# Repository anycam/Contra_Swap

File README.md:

# Contra_Swap
Contra Mechanical Keyboard Mod

Adding hotswap sockets pads, optional rotary encoder, oled screen and expansion points for uC's like nRFMicro.
Layout change made for 2x2u split space bars.
Still ProMicro compatibile, orientation changed, DAUGHTERBOARD REQUIRED !
Easy type C convertion.

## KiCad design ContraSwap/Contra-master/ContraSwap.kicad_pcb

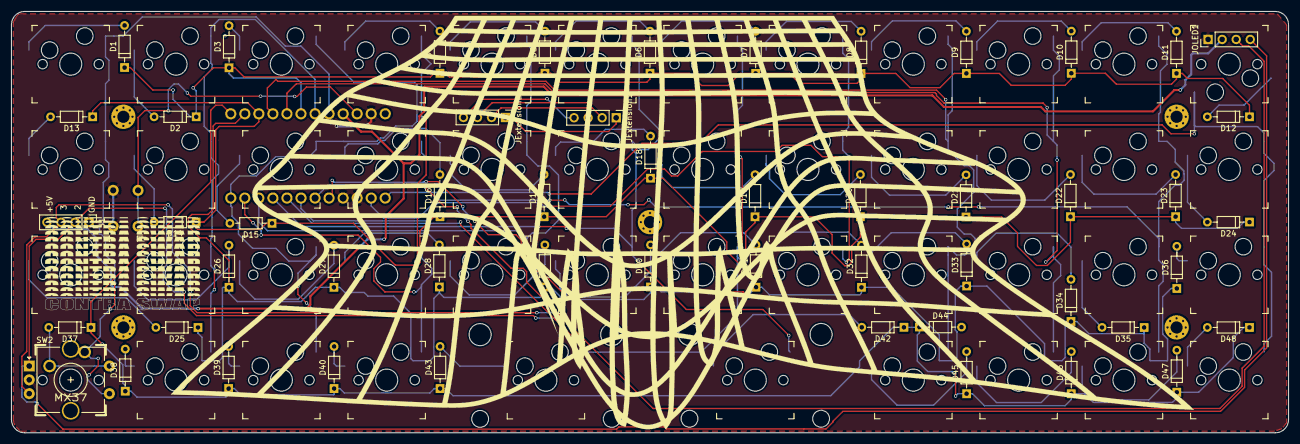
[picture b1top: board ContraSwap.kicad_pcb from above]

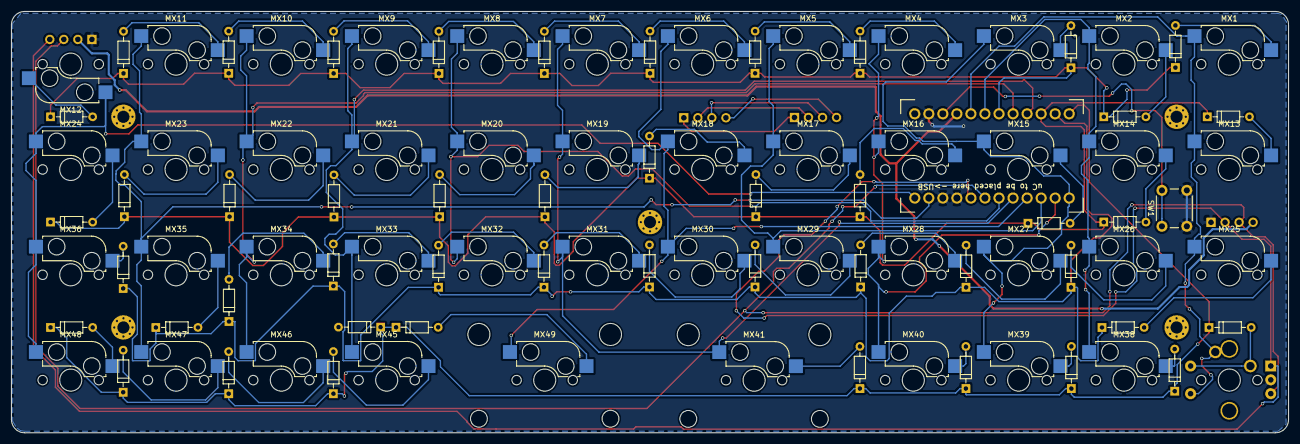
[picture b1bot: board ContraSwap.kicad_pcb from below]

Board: 2 copper layers, 231.0 x 76.2 mm, 102 parts (2 on the bottom side), 71 nets.

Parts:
D1, D2, D3, D4, D5, D6, D7, D8, D9, D10, D11, D12, D13, D14, D15, D16, D17, D18, D19, D20, D21, D22, D23, D24, D25, D26, D27, D28, D29, D30, D31, D32, D33, D34, D35, D36, D37, D38, D39, D40, D42, D43, D44, D45, D46, D47, D48: 1N4148; D_DO-35_SOD27_P7.62mm_Horizontal-DoubleSided
H1, H2: MountingHole; Stabilizer_MX_2u
J1: Conn_01x04; PinHeader_1x04_P2.54mm_Vertical
JExtension1: Conn_01x04; PinHeader_1x04_P2.54mm_Vertical
JExtensionL1: Conn_01x04; PinHeader_1x04_P2.54mm_Vertical
JOLED1: Conn_01x04; PinHeader_1x04_P2.54mm_Vertical
MX1, MX2, MX3, MX4, MX5, MX6, MX7, MX8, MX9, MX10, MX11, MX12, MX13, MX14, MX15, MX16, MX17, MX18, MX19, MX20, MX21, MX22, MX23, MX24, MX25, MX26, MX27, MX28, MX29, MX30, MX31, MX32, MX33, MX34, MX35, MX36, MX38, MX39, MX40, MX45, MX46, MX47, MX48: MX-1U; Kailh_socket_MX
MX37: MX-1U; MX_PCB_100H
MX41, MX49: MX-2U; Kailh_socket_MX
SW1: SW_PUSH; SW_PUSH_6mm
SW2: Rotary_Encoder_Switch; RotaryEncoder_Alps_EC11E-Switch_Vertical_H20mm_CircularMoun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
U1: ProMicro; pro_micro

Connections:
+5V: J1.4, JOLED1.2, U1.21
COL0: MX1.1, MX13.1, MX25.1, MX37.1, SW2.S1, U1.20
COL1: MX2.1, MX14.1, MX26.1, MX38.1, U1.19
COL2: MX3.1, MX15.1, MX27.1, MX39.1, U1.12
COL3: MX4.1, MX16.1, MX28.1, MX40.1, U1.11
COL4: MX5.1, MX17.1, MX29.1, U1.10
COL5: MX6.1, MX18.1, MX30.1, MX49.1, U1.9
COL6: MX7.1, MX19.1, MX31.1, MX41.1, U1.8
COL7: MX8.1, MX20.1, MX32.1, U1.7
COL8: MX9.1, MX21.1, MX33.1, MX45.1, U1.16
COL9: MX10.1, MX22.1, MX34.1, MX46.1, U1.17
COL10: MX11.1, MX23.1, MX35.1, MX47.1, U1.2
COL11: MX12.1, MX24.1, MX36.1, MX48.1, U1.1
GND: J1.1, JOLED1.1, SW1.2, SW2.C, U1.3, U1.4, U1.23
unnamed: D1.2, MX1.2
unnamed: D2.2, MX2.2
unnamed: D3.2, MX3.2
unnamed: D4.2, MX4.2
unnamed: D5.2, MX5.2
unnamed: D6.2, MX6.2
unnamed: D7.2, MX7.2
unnamed: D8.2, MX8.2
unnamed: D9.2, MX9.2
unnamed: D10.2, MX10.2
unnamed: D11.2, MX11.2
unnamed: D12.2, MX12.2
unnamed: D13.2, MX13.2
unnamed: D14.2, MX14.2
unnamed: D15.2, MX15.2
unnamed: D16.2, MX16.2
unnamed: D17.2, MX17.2
unnamed: D18.2, MX18.2
unnamed: D19.2, MX19.2
unnamed: D20.2, MX20.2
unnamed: D21.2, MX21.2
unnamed: D22.2, MX22.2
unnamed: D23.2, MX23.2
unnamed: D24.2, MX24.2
unnamed: D25.2, MX25.2
unnamed: D26.2, MX26.2
unnamed: D27.2, MX27.2
unnamed: D28.2, MX28.2
unnamed: D29.2, MX29.2
unnamed: D30.2, MX30.2
unnamed: D31.2, MX31.2
unnamed: D32.2, MX32.2
unnamed: D33.2, MX33.2
unnamed: D34.2, MX34.2
unnamed: D35.2, MX35.2
unnamed: D36.2, MX36.2
unnamed: D37.2, MX37.2, SW2.S2
unnamed: D38.2, MX38.2
unnamed: D39.2, MX39.2
unnamed: D40.2, MX40.2
unnamed: D42.2, MX49.2
unnamed: D43.2, MX41.2
unnamed: D45.2, MX45.2
unnamed: D46.2, MX46.2
unnamed: D47.2, MX47.2
unnamed: D48.2, MX48.2
unnamed: JExtension1.1, JExtensionL1.1
unnamed: JExtension1.2, JExtensionL1.2
unnamed: JExtension1.3, JExtensionL1.3
unnamed: JExtension1.4, JExtensionL1.4
unnamed: SW1.1, U1.22
PIN2SDA: J1.2, JOLED1.4, SW2.A, U1.5
PIN3SCL: J1.3, JOLED1.3, SW2.B, U1.6
ROW0: D1.1, D2.1, D3.1, D4.1, D5.1, D6.1, D7.1, D8.1, D9.1, D10.1, D11.1, D12.1, U1.18
ROW1: D13.1, D14.1, D15.1, D16.1, D17.1, D18.1, D19.1, D20.1, D21.1, D22.1, D23.1, D24.1, U1.15
ROW2: D25.1, D26.1, D27.1, D28.1, D29.1, D30.1, D31.1, D32.1, D33.1, D34.1, D35.1, D36.1, U1.14
ROW3: D37.1, D38.1, D39.1, D40.1, D42.1, D43.1, D44.1, D45.1, D46.1, D47.1, D48.1, U1.13

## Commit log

2022-02-20 Adding files.
    Hello there!
2022-02-20 Readme
    Adding info
2022-03-23 Adding images
    Images to illustrate digital life systems translated to real time eco systems
2022-03-23 Adding eyes.
